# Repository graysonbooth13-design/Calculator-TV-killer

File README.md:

# Calculator-TV-killer
This is going to be an open source battery powered calculator further more containing a IR LED To turn off LED's and such.

Calculator-TV-killer
This is my second GitHub repo so it is a work in progress but I built this calculator for schoool and to just have fun
If you have any ideas or concerns I am fully open to critisism just leave a comment! :)

CALCULATOR-TV-KILLER
GRAYSONS MACRO MACHINE is a 16 key calculator. It also has A IR LED to turn off tv's, and uses arduino IDE code

Features:
2 peice 3d printed case. Custom colors ooooohhh.
1 IR LEDs. these should work as a TV killer for TV's.
5 Keys!
CADModel:

It has 2 seperate printed pieces. The base where the PCB sits, and the top cover.

Schematic:

Made in KiCAd.

PCB:

3d file of the PCB (With components =>)

Here's my PCB! It was made in KiCad.

BOM:

"Id";"Designator";"Footprint";"Quantity";"Designation";"Supplier and ref";
1;"D18,D8,D7,D9,D14,D2,D4,D6,D12,D17,D10,D3,D13,D11,D15,D16";"DIOAD753W49L380D172B";16;"1N4148";;;
2;"SW5,SW2,SW1,SW7,SW3,SW/1,SW0,SW-1,SW6,SW_DEL1,SW=1,SW+1,SW4,SW9,SW*1,SW8";"SW_Cherry_MX_1.00u_PCB";16;"SW_Push";;;
3;"Q1";"TO-92L_Inline";1;"NPN";;;
4;"R1";"R_Axial_DIN0204_L3.6mm_D1.6mm_P5.08mm_Horizontal";1;"4.7 Kohms";;;
5;"R2";"R_Axial_DIN0204_L3.6mm_D1.6mm_P5.08mm_Horizontal";1;"39 ohms";;;
6;"Brd1";"MODULE_DM-OLED096-636";1;"SSD1306";;;
7;"U1";"XIAO-RP2040-DIP";1;"XIAO-RP2040-DIP";;;
8;"D1";"LED_D5.0mm_IRGrey";1;"Super-bright 5mm IR LED - 940nm";;;

(Above is the CSV version of the BOM and below is just normal)

Here should be everything you need to make this hackpad

16x Cherry MX Blue Switches $7.00

16x DSA Keycaps that have "1-9 and zero and +,-,DIvide, del, and =" $0.00 will 3d print

4x M4x6 Heatset inserts $9.00 in kit with bolts

4x M4x4mm Heat set inserts from CNC kitchen

16X 1N4148 Diode $6.00

1x XIAO RP2040 $4.00

1X SSD1306 0.96 inch 128X64 pixel IC2 OLED $7.00

2X Resistors 1, 39 ohm and 1, 4.7 K ohms $9.00

1X Super-bright 5mm IR LED - 940nm   $0.75 from https://www.adafruit.com/product/387?srsltid=AfmBOopKEtXa5r7NFesDsghJSTXoIFfyz0MSlwi3U7XEUNElIbBDi-1RI1c 

1X 2N2222A NpN transistor $9.00

1x Case (2 printed parts)

Links to parts:

(Key switches: https://www.amazon.com/Fejwlvs-Pre-Lubricated-Dustproof-Mechanical-Keyboards、MX/dp/B0GFLWMHY3/ref=sr_1_5_sspa?crid=3TJCBFA8PGTQK&dib=eyJ2IjoiMSJ9.MUELtzarVPh1NqYa3EK1EJX_g7YVVKb-c7MwhJsWGQ344GIhIl-PX6bq-dzCIrdG2ZZSXJkA5gzC0x911H3jToB145t_VOCoupObny0bRJfZM-_c-W2LrwPkR_oeFhJsg147z1ndf54UBGYbY7ICptbjB0E-_0nWCnNexu8NyoJ7gpnpGRNZTVOjRBUkvVUtIj_MfOLu_XL7Y48IlwUBEG8ISojdYuzAm5yTf8BuM1A.fPJX89Ir0riDGDDwBn1CHYfFr8JJkA3AthyHhh7_-Gg&dib_tag=se&keywords=Cherry%2BMX%2BSwitches%2Bassortment&qid=1770771376&sprefix=cherry%2Bmx%2Bswitches%2Bassortment%2Caps%2C311&sr=8-5-spons&sp_csd=d2lkZ2V0TmFtZT1zcF9tdGY&th=1)

(M4 SCREWS: https://www.amazon.com/VGBUY-600pcs-Assortment-Printer-Stainless/dp/B0D1XJ766V/ref=sr_1_3?crid=DU098LO3QODD&dib=eyJ2IjoiMSJ9.Du6eKz-vfO0otk5mZ1epwb26hK4HILY0qCvZQ6E4-VgU6e89cluUXjtjfZIvUGbF9NxRdzD5YhClawBfZFMASpfWCuKk22x7URdzAubaEadEBMZ6Rh09zVvdqkRiFQFjiRSGrwzi5Qe1ccEfKJeyasZTVNNAr9eHwwp1YlTueobPvoCKJ3l9Rvi7OVN7y6AQWVRzJQ41PTKSk8AiO-tfXMYKcVn9QrPtTXP5sRsfFuM.wu_jUhdkO1ThY-q4n_EelO83HTC5mmx34PS2apULzZo&dib_tag=se&keywords=m3%2Bscrew%2Bkit&qid=1770772225&sprefix=m3%2B%2Caps%2C393&sr=8-3&th=1)

(Diode's: https://www.amazon.com/EEEEE-Switching-MILLIAMP-Electronic-Silicon/dp/B0FC289DVH/ref=sr_1_3?adgrpid=187993647764&dib=eyJ2IjoiMSJ9.09kb66VxlBzN6HV_K6vi9c3BtsT_GWIPLEMOancfoBooOv5sAhUe0KJrpccH8oIJbFJ1coaWUnv1i5DlAVBA3kbCZuk955cUs34FZ8ectndBFcRl1BKHD615JLLndPvKXpMQibx0KPeYs7Pfwm11T47iHx91AOU_NtuFRmZ-S6ZTVdhFIRA6xDMAZ3EsCo7A4Mc5Ceq0WJoWEiMsRLqAt-2GGjcp-vMOh658Zf6EMaQ.i8j7rV67SDP0j3WiHW-2NAeSR0HlO6Gm_Qic2Eam-7s&dib_tag=se&hvadid=779642773176&hvdev=c&hvexpln=0&hvlocphy=1015431&hvnetw=g&hvocijid=17401088717729557827--&hvqmt=e&hvrand=17401088717729557827&hvtargid=kwd-1460322120&hydadcr=3018_13539028_2128636&keywords=1n4148%2Bdiode&mcid=f2eeec0b3b1a399ca0829126fa611e7c&qid=1770772333&sr=8-3&th=1)

(Xiao rp2040: https://www.seeedstudio.com/XIAO-RP2040-v1-0-p-5026.html?srsltid=AfmBOopbY1dPG0hkWRmuq-8IblETa4FKZI_A_LwXS7W4cyi72GPG5dC0)

(Oled: https://www.amazon.com/HiLetgo-Serial-128X64-Display-Color/dp/B06XRBYJR8/ref=sr_1_14?dib=eyJ2IjoiMSJ9.-ICP_fsWugdKDgQgSChofrz_cxu5gXXrIqC7Oti8ouBA6k22EBIip1KIDQkzeUzAM3TIGEcGFmhTq4kUNLDraTARmFcZWe2e5xJTCVNmV0Zqru5ayaqTzVTfmVSKK1vPKlhdlyfTbvsVwAUeM8U0_QspdKzwU3r-hVGchVoB8YxghW9QmqtIMhSRpyuK1w3d92oOKPxZLqb7Dx4uWkj8t7PktWAoiKCEelgmlDdEpgs.bLAaVfHUDtO_f-E_t68LlBmzt6VLDGur_D5G8TdRrvM&dib_tag=se&keywords=ssd1306%2Boled%2Bdisplay&qid=1770772525&sr=8-14&th=1)

(Resistors: https://www.amazon.com/ALLECIN-4W-Film-Resistor-Kit/dp/B0CDWW5BFH/ref=sr_1_2_sspa?crid=2GFJNXM111L61&dib=eyJ2IjoiMSJ9.QqtzmCG7CKt6OW1fHgTb26uI1Fk5beBArSayNzxiB8Q5PfdVBH_fHO-i8Oq2qY-fWR7yyRFHSOeC2RmG0E7w0mtYXMe7donOE8TLqFJXOTNzKCJuCvEQlzEzyaf3O-5D_cGpYC_4Fr3yk3Cr-o6ynATg4hoUh2RQ702TuOH8x5eLmKRUgMbPIwMs_D7sSJRQNzIp690U9bqkzdZqwfkoHmcEW4ZQApPpl7A3RfpMR0I.rNj68d3atHfDnVFBy4if--2BnhPglSZ4rxG2vOnEO3s&dib_tag=se&keywords=resistor%2Bkit&qid=1770772812&sprefix=resistorr%2Bkit%2Caps%2C245&sr=8-2-spons&sp_csd=d2lkZ2V0TmFtZT1zcF9hdGY&th=1)

(Transistors: https://www.amazon.com/ALLECIN-BJT-Transistor-Kit-Transistors/dp/B0C1V82313/ref=sr_1_6_sspa?adgrpid=185130291583&dib=eyJ2IjoiMSJ9.VsgPg0CpoSmLDBqmaiKemioTeubimeA5gbMHrCVETlLHuISg-KQ_TrgB12GRq8EUaYy89mM0c8-gk-RRM7sUZ8OY_KPwAymbrb3ne8DceQ6rNBHwQu6SpnO7aX1fF-uOq3RHPGw6mCcCi4gI_n7mZHaYhRP6ijxiwM2Nf_gKmGpQ-FS1_OmSGLsohkzApgw1RSXm4t1kRg-nTRCBaIXqIqptj6rTDNmtVQwazBJiD4g.agcjYWhGehzE-07sqCxWXgNTTte9UZ4l36FKaob2p5g&dib_tag=se&hvadid=779721006957&hvdev=c&hvexpln=0&hvlocphy=1015431&hvnetw=g&hvocijid=13743219906590360801--&hvqmt=e&hvrand=13743219906590360801&hvtargid=kwd-323540961971&hydadcr=24632_13858459_8069&keywords=2n2222a+npn+transistor&mcid=a2ab655ea30438a0a56edb22fa9e6f95&qid=1770773008&sr=8-6-spons&sp_csd=d2lkZ2V0TmFtZT1zcF9tdGY&psc=1)

(heat set inserts: https://cnckitchenus.store/products/heat-set-insert-m4-x-4-short-version-100-pieces)

JOKE TIMMEEEEEE
What happenes when you eat tinfoil

you...sheet metal :)

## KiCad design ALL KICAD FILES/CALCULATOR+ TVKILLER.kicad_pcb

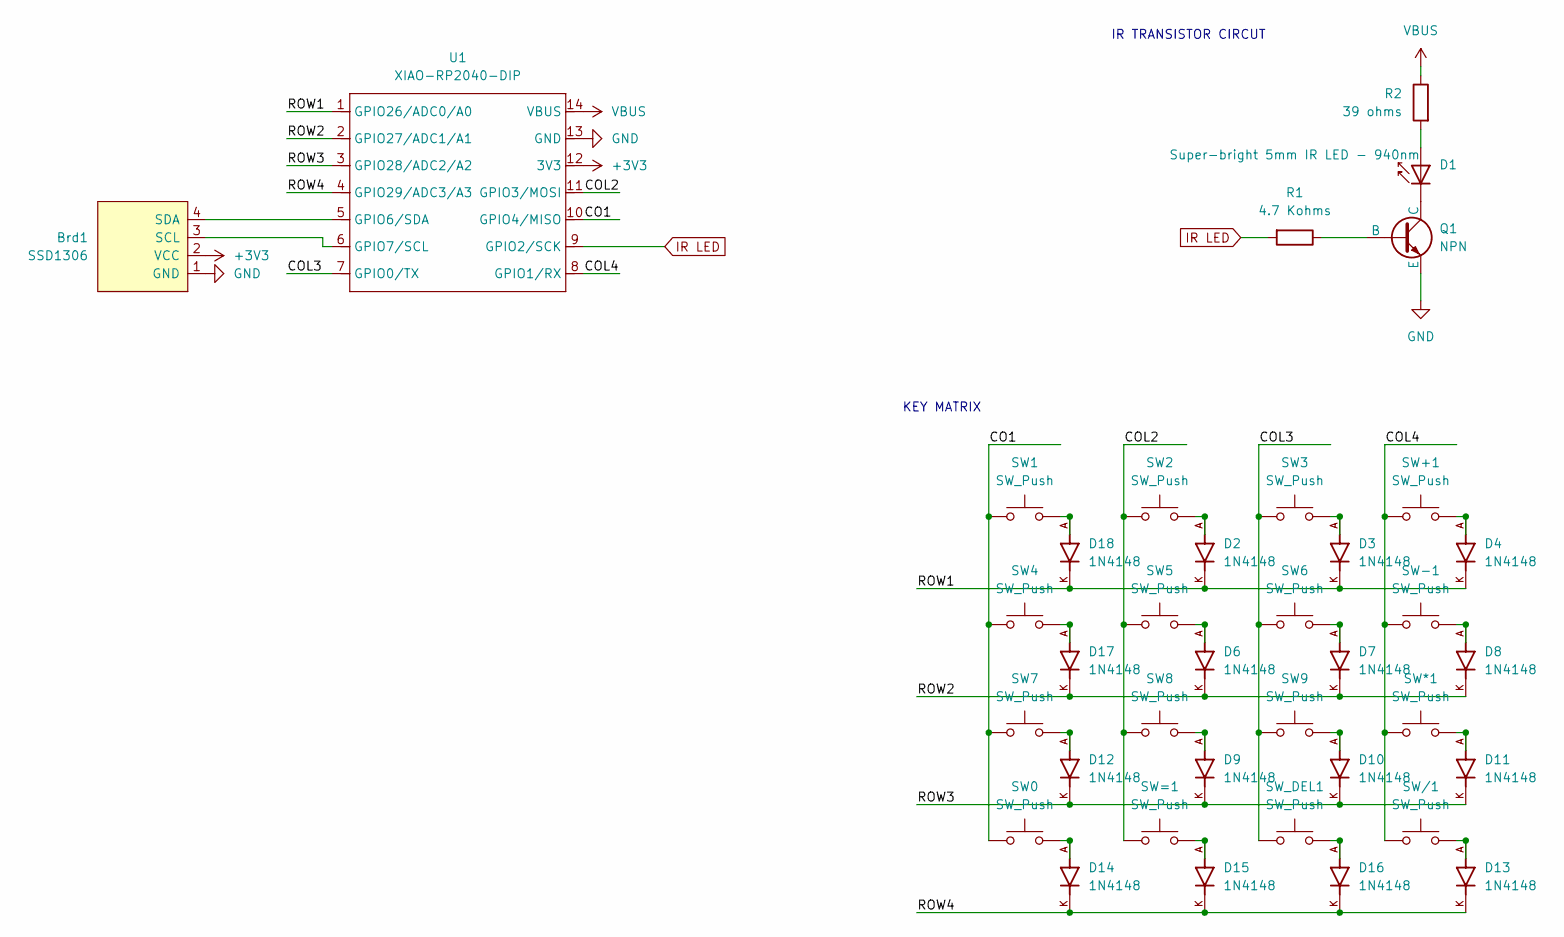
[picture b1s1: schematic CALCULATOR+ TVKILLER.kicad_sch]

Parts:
Brd1: SSD1306; MODULE_DM-OLED096-636
D1: Super-bright 5mm IR LED - 940nm; LED_D5.0mm_IRGrey
D2, D3, D4, D6, D7, D8, D9, D10, D11, D12, D13, D14, D15, D16, D17, D18: 1N4148; DIOAD753W49L380D172B; PARTREV 5; DigiKey_Part_Number 1N4148FS-ND
Q1: NPN; TO-92L_Inline
R1: 4.7 Kohms; R_Axial_DIN0204_L3.6mm_D1.6mm_P5.08mm_Horizontal
R2: 39 ohms; R_Axial_DIN0204_L3.6mm_D1.6mm_P5.08mm_Horizontal
SW0, SW1, SW2, SW3, SW4, SW5, SW6, SW7, SW8, SW9: SW_Push; SW_Cherry_MX_1.00u_PCB
SW*1: SW_Push; SW_Cherry_MX_1.00u_PCB
SW+1: SW_Push; SW_Cherry_MX_1.00u_PCB
SW-1: SW_Push; SW_Cherry_MX_1.00u_PCB
SW/1: SW_Push; SW_Cherry_MX_1.00u_PCB
SW=1: SW_Push; SW_Cherry_MX_1.00u_PCB
SW_DEL1: SW_Push; SW_Cherry_MX_1.00u_PCB
U1: XIAO-RP2040-DIP

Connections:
+3V3: Brd1.2 (VCC), U1.12 (3V3)
/CO1: SW0.1, SW1.1, SW4.1, SW7.1, U1.10 (GPIO4/MISO)
/COL2: SW2.1, SW5.1, SW8.1, SW=1.1, U1.11 (GPIO3/MOSI)
/COL3: SW3.1, SW6.1, SW9.1, SW_DEL1.1, U1.7 (GPIO0/TX)
/COL4: SW*1.1, SW+1.1, SW-1.1, SW/1.1, U1.8 (GPIO1/RX)
/ROW1: D2.K, D3.K, D4.K, D18.K, U1.1 (GPIO26/ADC0/A0)
/ROW2: D6.K, D7.K, D8.K, D17.K, U1.2 (GPIO27/ADC1/A1)
/ROW3: D9.K, D10.K, D11.K, D12.K, U1.3 (GPIO28/ADC2/A2)
/ROW4: D13.K, D14.K, D15.K, D16.K, U1.4 (GPIO29/ADC3/A3)
GND: Brd1.1 (GND), Q1.3 (E), U1.13 (GND)
IR LED: R1.2, U1.9 (GPIO2/SCK)
unnamed: Brd1.3 (SCL), U1.6 (GPIO7/SCL)
unnamed: Brd1.4 (SDA), U1.5 (GPIO6/SDA)
unnamed: D1.2 (A), R2.2
unnamed: D1.1 (K), Q1.1 (C)
unnamed: D2.A, SW2.2
unnamed: D3.A, SW3.2
unnamed: D4.A, SW+1.2
unnamed: D6.A, SW5.2
unnamed: D7.A, SW6.2
unnamed: D8.A, SW-1.2
unnamed: D9.A, SW8.2
unnamed: D10.A, SW9.2
unnamed: D11.A, SW*1.2
unnamed: D12.A, SW7.2
unnamed: D13.A, SW/1.2
unnamed: D14.A, SW0.2
unnamed: D15.A, SW=1.2
unnamed: D16.A, SW_DEL1.2
unnamed: D17.A, SW4.2
unnamed: D18.A, SW1.2
unnamed: Q1.2 (B), R1.1
VBUS: R2.1, U1.14 (VBUS)

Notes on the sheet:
IR TRANSISTOR CIRCUT
KEY MATRIX

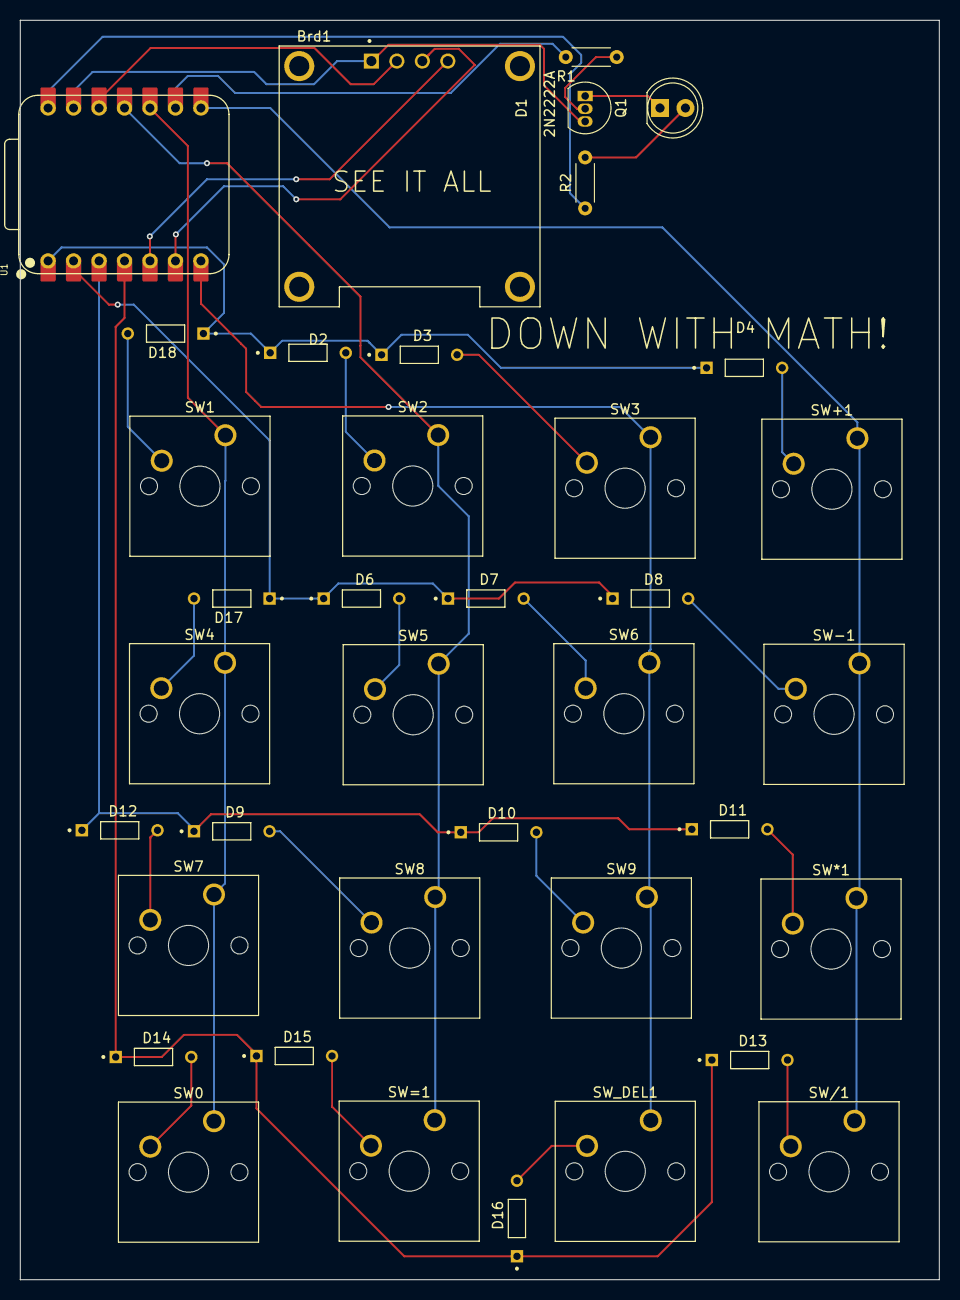
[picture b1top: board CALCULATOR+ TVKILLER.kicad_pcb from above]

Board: 2 copper layers, 91.6 x 125.5 mm, 38 parts (0 on the bottom side), 33 nets.

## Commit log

2026-01-31 Enhance README with project details and features
    Expanded the README with detailed project information, features, schematics, and BOM.
2026-02-01 Update README with new images and descriptions
2026-02-03 Add PCB image to README
    Added a new image of the PCB to the README.
2026-02-04 Add new file S with initial content
2026-02-09 Add new file 's' in 3D files directory
2026-02-10 Add initial calculator functionality with IR control
2026-02-10 Add USB-C lanyard to README
    Added a USB-C to USB-C lanyard for powering.
2026-02-11 Add prices and links for components in README
    Updated the README.md to include prices for components and added links to parts.
2026-02-12 Create BOM/s file
2026-02-21 Update BOM section with new components
    Added new components to the BOM section in the README.
2026-02-24 Remove Usb-C to Usb-C lanyard from README
    Removed the Usb-C to Usb-C lanyard from the parts list.
2026-02-24 Update hardware component specifications and links
